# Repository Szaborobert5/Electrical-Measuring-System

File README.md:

# Electrical Measuring System

The PCB was designed in KiCad and firmware was written in STM32CubeIDE. The goal of this project is to develop a device that can measure AC/DC voltage, AC frequency, active power and active energy consumption. This PCB has two layers(signal and ground). 

## Block diagram

The system is divided in 4 sub-systems.

It consists of the following :

- Power supply section
- Microcontroller STM32
- Measuring chip ATM90E26
- OLED Diplay

SPI communication is used for ATM90E26 and OLED display. SWD is used for microcontroller programming. A buck converter is used for power supply

## PCB and Schematic in KiCad

# Firmware

Firmware runs on an **STM32G431K8T6**, reads AC frequency, active power and active energy consumption from an **ATM90E26** metering IC over SPI, and shows the results on an colour display. A push button switches between four screens.

## Firmware architecture

| Module | Files | Responsibility |
|---|---|---|
| Application | `main.c` | Initialisation, 500 ms measurement loop, button handling |
| Metering driver | `atm90e26.c/.h` | ATM90E26 register access, configuration, scaling to physical units |
| Display driver | `st7789.c/.h` | ST7789 initialisation, pixels, lines, rectangles, circles, arcs, text |
| UI | `screens.c/.h` | The four screens, sparkline history, min / max tracking |
| Fonts | `font.c/.h` | Bitmap fonts: 7×10, 11×18, 16×26 |
| Platform | `stm32g4xx_hal_msp.c`, `stm32g4xx_it.c`, `system_stm32g4xx.c`, `syscalls.c`, `sysmem.c` | CubeMX-generated HAL, interrupt and newlib support |

All measurements are stored in one global structure, `g_energy` (`EnergyData_t`), which the metering driver writes and the UI reads.

## Repository structure

```
Core/
  Inc/                        main.h, atm90e26.h, st7789.h, screens.h, font.h, tests.h, ...
  Src/
    main.c                    Application and main loop
    atm90e26.c                Metering IC driver
    st7789.c                  Display driver
    screens.c                 UI screens
    font.c                    Bitmap fonts
    tests.c                   Self-test suite
    stm32g4xx_it.c            Interrupt handlers
    stm32g4xx_hal_msp.c       HAL MSP (SPI1 pins and clocks)
    system_stm32g4xx.c        CMSIS system init
    syscalls.c, sysmem.c      newlib support
Drivers/                      STM32G4 HAL and CMSIS (generated)
Display_Screens.ioc           STM32CubeMX configuration
STM32G431K8TX_FLASH.ld        Linker script
Display_Screens.launch        Run configuration
Display_Screens_Debug.launch  Debug configuration
```

## Testing

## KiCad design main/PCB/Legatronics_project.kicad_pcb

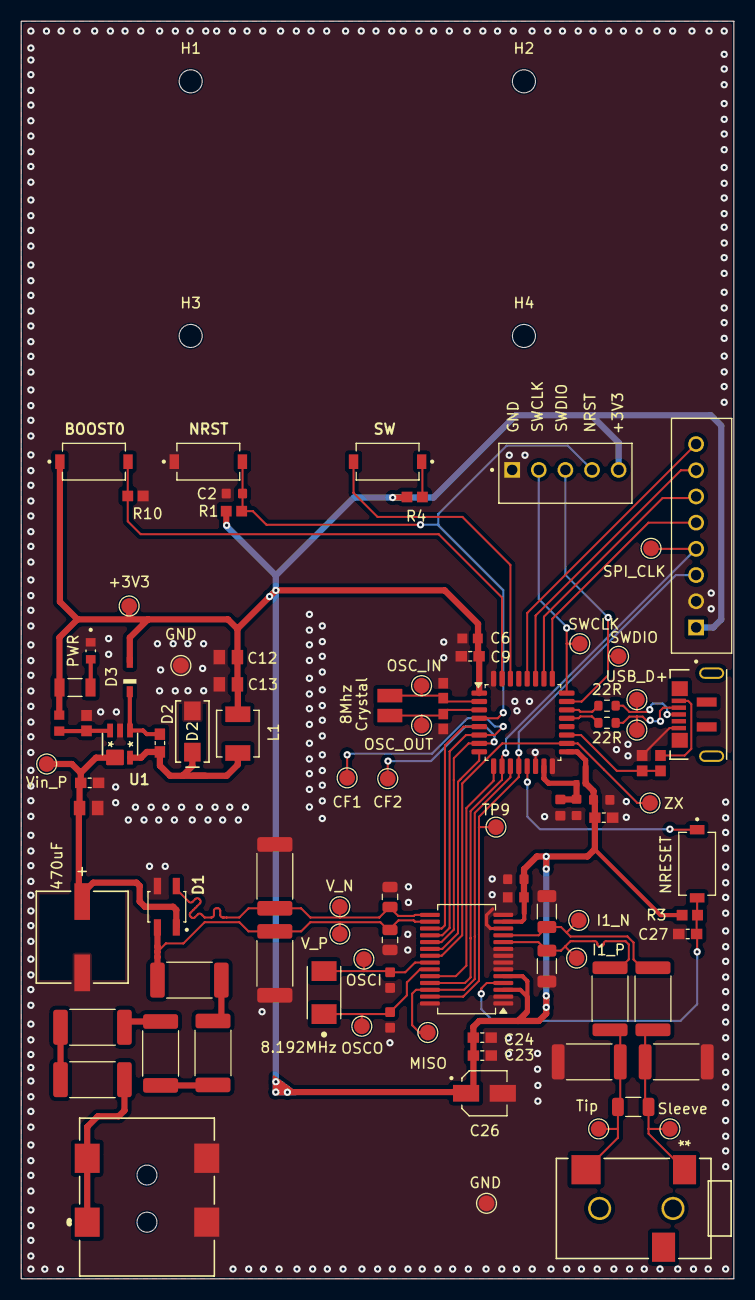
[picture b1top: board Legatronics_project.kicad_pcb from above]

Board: 2 copper layers, 68.0 x 120.0 mm, 98 parts (0 on the bottom side), 50 nets.

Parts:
+3V3: 3V3; TestPoint_Pad_D1.5mm
C1, C3: 8p; CAPC1608X90N
C2, C11, C14, C17: 1uF; CAPC1608X90N
C4: 470uF; PCAP_8x10-ELECT_NCA
C5, C8, C9, C23, C24, C27: 100nF; CAPC1608X90
C6: 4.7uF; CAPC1608X90N
C7, C12, C13: 10uF; CAPC2012X135N
C10: 10nF; CAPC1608X90N
C16, C21: 330nF; C_1206_3216Metric
C18: 1nF; CAPC1608X90N
C19, C20: 33nF; C_0805_2012Metric
C22, C25: 12p; CAPC1608X87N
C26: 10uF; CAP_EEE1CA100SR
CF1: CF1; TestPoint_Pad_D1.5mm
CF2: CF2; TestPoint_Pad_D1.5mm
Cboost1: 100nF; CAPC1608X90
D1: CBRHDSH2-40 TR13 PBFREE; SOIC180P460X187-4N
D2: B240; SMA_DIO-L
D3: 1N4148WS; SODFL2512X100N
D4: PWR; LEDC1608X35N
ECS-81.92-12-30Q-EN-TR1: 8.192MHz; XTAL_ECS-81.92-12-30Q-EN-TR
FB1: 120; BEADC1005X55N
GND: GND; TestPoint_Pad_D1.5mm
GND#2: GND; TestPoint_Pad_D1.5mm
H1, H2, H3, H4: MountingHole; MountingHole_2.2mm_M2
J1: USB-B-1051640001; CON00906_5_MOL
J2: Conn_01x05_Pin; TE_640456-5
J3: PJ-002AH-SMT-TR; PJ-002AH-SMT-TR_CUD
J4: SJ-3523-SMT-TR; SJ-3523-SMT_CUD
J5: B8B-XH-A; JST_B8B-XH-A
L1: 15uH; IND_SRP4020TA-150M
MISO: MISO; TestPoint_Pad_D1.5mm
NDK–STDCRA3-8M1: 8Mhz; XTAL_NX3225GD-8MHZ-STD-CRA-3_NDK
NRESET: PTS636_SM43J_SMTR_LFS; SW_PTS636_SM43J_SMTR_LFS
OSCI: OSCI; TestPoint_Pad_D1.5mm
OSCO: OSCO; TestPoint_Pad_D1.5mm
OSC_IN: OSC_IN; TestPoint_Pad_D1.5mm
OSC_OUT: OSC_OUT; TestPoint_Pad_D1.5mm
R1, R3, R4, R6, R10: 10k; RESC1607X60N
R5: 31.6k; RESC1508X55N
R7, R8: 22R; R_0603_1608Metric
R9: 62R; RESC3116X65N
R12, R13: 100R; R_2512_6332Metric
R14, R18, R19, R20, R21: 3.6k; R_2512_6332Metric_Pad1.40x3.35mm_HandSolder
R15, R16: 2R4; R_2512_6332Metric
R17: 51R; R_1206_3216Metric
R22: 33k; RESC1607X60N
R23: 82k; RESC1607X60N
R24, R25: 1k; R_2512_6332Metric_Pad1.40x3.35mm_HandSolder
S1, S2, S4: PTS636_SM43J_SMTR_LFS; SW_PTS636_SM43J_SMTR_LFS
SPI_CLK: SPI_SCK; TestPoint_Pad_D1.5mm
SWCLK: SWCLK; TestPoint_Pad_D1.5mm
SWDIO: SWDIO; TestPoint_Pad_D1.5mm
Sleeve: Sleeve; TestPoint_Pad_D1.5mm
TP3: I1_P; TestPoint_Pad_D1.5mm
TP4: I1_N; TestPoint_Pad_D1.5mm
TP9: MOSI; TestPoint_Pad_D1.5mm
TP22: Vin_P; TestPoint_Pad_D1.5mm
Tip: Tip; TestPoint_Pad_D1.5mm
U1: MCP16301x-xCH; SOT-23-6_MC_MCH
U2: STM32G431K6Tx; LQFP-32_7x7mm_P0.8mm
U3: ATM90E26-YU; SSOP-28_5.3x10.2mm_P0.65mm
USB_D+: USB_D+; TestPoint_Pad_D1.5mm
USB_D-: USB_D-; TestPoint_Pad_D1.5mm
V_N: IN2_N; TestPoint_Pad_D1.5mm
V_P: V_P; TestPoint_Pad_D1.5mm
ZX: ZX; TestPoint_Pad_D1.5mm

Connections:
+3V3: +3V3.1 (1_1), C6.1, C8.1, C9.1, C12.1, C13.1, C14.1, C17.1, C18.1, C23.1, C24.1, C26.1, D3.A, FB1.2, J2.5, J5.1, L1.2, R1.1, R3.2, R4.1, R5.1, R9.1, S2.1, U2.1 (VDD), U2.17 (VDD), U3.3 (DVDD), U3.5 (AVDD), U3.13 (Vref)
/BOOT0: R10.2, S2.2, U2.31 (PB8)
/Boost: Cboost1.1, D3.C, U1.1 (BOOST)
/CF1: CF1.1 (1_1), U2.6 (PA1), U3.18 (CF1)
/CF2: CF2.1 (1_1), U2.7 (PA2), U3.19 (CF2)
/CS2: U2.9 (PA4), U3.24 (~CS)
/I1_N: C16.2, R13.2, TP4.1 (1_1), U3.11 (I1N)
/I1_P: C21.1, R12.2, TP3.1 (1_1), U3.10 (I1P)
/IRQ: U2.8 (PA3), U3.20 (IRQ)
/LED_A: D4.2, R9.2
/NRESET: NRESET.1, U2.13 (PB0)
/NRST: C2.1, J2.4, R1.2, S1.2, U2.4 (PG10)
/OSCI: C25.1, ECS-81.92-12-30Q-EN-TR1.2, OSCI.1 (1_1), U3.22 (OSCI)
/OSCO: C22.1, ECS-81.92-12-30Q-EN-TR1.1, OSCO.1 (1_1), U3.23 (OSCO)
/OSC_IN: C3.1, NDK–STDCRA3-8M1.2, OSC_IN.1 (1_1), U2.2 (PF0)
/OSC_OUT: C1.1, NDK–STDCRA3-8M1.1, OSC_OUT.1 (1_1), U2.3 (PF1)
/PA9_USB: R22.2, R23.1, U2.19 (PA9)
/PA15_CS1: J5.5, U2.25 (PA15)
/PB3_DISPLAY: J5.6, U2.26 (PB3)
/PB4_RST: J5.7, U2.27 (PB4)
/PB5_BL: J5.8, U2.28 (PB5)
/PB7_SW2: S4.2, U2.30 (PB7)
/SPI_MISO: MISO.1 (1_1), U2.11 (PA6), U3.26 (SDO/UTX)
/SPI_MOSI: J5.3, TP9.1 (1_1), U2.12 (PA7), U3.27 (SDI/URX)
/SPI_SCK: J5.4, SPI_CLK.1 (1_1), U2.10 (PA5), U3.25 (SCLK)
/SW: Cboost1.2, D2.1 (K), L1.1, U1.6 (SW)
/SWCLK: J2.2, SWCLK.1 (1_1), U2.24 (PA14)
/SWDIO: J2.3, SWDIO.1 (1_1), U2.23 (PA13)
/Sleeve: J4.1 (SLEEVE), R13.1, R16.1, R17.1, Sleeve.1 (1_1)
/Tip: J4.2 (TIP), R12.1, R15.2, R17.2, Tip.1 (1_1)
/USB_D+: J1.3, R8.2, USB_D+.1 (1_1)
/USB_D-: J1.2, R7.2, USB_D-.1 (1_1)
/VBUS: J1.1, R22.1
/VDDA: C10.1, C11.1, FB1.1, U2.15 (VDDA)
/VIn_P: C4.1, C5.1, C7.1, D1.1 (+), TP22.1 (1_1), U1.4 (EN), U1.5 (V_{IN})
/V_N: C20.1, D1.2, R25.2, U3.15 (VN), V_N.1 (1_1)
/V_P: C19.1, D1.4, R21.2, R24.2, U3.16 (VP), V_P.1 (1_1)
/Vfb: R5.2, R6.1, U1.3 (Vfb)
/WO: U2.5 (PA0), U3.17 (WarnOut)
/ZX: U2.18 (PA8), U3.21 (ZX), ZX.1 (1_1)
/uC_D+: R8.1, U2.22 (PA12)
/uC_D-: R7.1, U2.21 (PA11)
GND: C1.2, C2.2, C3.2, C4.2, C5.2, C6.2, C7.2, C8.2, C9.2, C10.2, C11.2, C12.2, C13.2, C14.2, C16.1, C17.2, C18.2, C19.2, C20.2, C21.2, C22.2, C23.2, C24.2, C25.2, C26.2, C27.2, D1.3 (-), D2.2 (A), D4.1, GND.1 (1_1), GND#2.1 (1_1), J1.5, J2.1, J3.2, J3.3, J5.2, R6.2, R10.1, R15.1, R16.2, R23.2, R24.1, R25.1, S1.1, U1.2 (GND), U2.14 (VSSA), U2.16 (VSS), U2.32 (VSS), U3.1 (MMD1), U3.2 (DGND), U3.6 (AGND), U3.7 (I2P), U3.8 (I2N), U3.9 (DGND), U3.12 (USEL), U3.14 (AGND), U3.28 (MMD0)
unnamed: J3.1A, J3.1B, R14.1
unnamed: R4.2, S4.1
unnamed: R14.2, R18.1
unnamed: R18.2, R19.1
unnamed: R19.2, R20.1
unnamed: R20.2, R21.1
unnamed: C27.1, NRESET.2, R3.1, U3.4 (~Reset)

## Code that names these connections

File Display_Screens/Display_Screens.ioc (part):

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Mcu.Name=STM32G431K(6-8-B)Tx
Mcu.Package=LQFP32
Mcu.UserName=STM32G431K8Tx
PA0.GPIOParameters=GPIO_Label
PA0.GPIO_Label=WarnOut
PA0.Signal=GPIO_Input
PA1.GPIOParameters=GPIO_Label
PA1.GPIO_Label=CF1
PA1.Signal=GPIO_Input
PA13.Mode=Serial_Wire
PA13.Signal=SYS_JTMS-SWDIO
PA14.Mode=Serial_Wire
PA14.Signal=SYS_JTCK-SWCLK
PA15.GPIOParameters=GPIO_Speed,PinState,GPIO_Label
PA15.GPIO_Label=CS_ST7789
PA15.GPIO_Speed=GPIO_SPEED_FREQ_HIGH
PA15.PinState=GPIO_PIN_SET
PA15.Signal=GPIO_Output
PA2.GPIOParameters=GPIO_Label
PA2.GPIO_Label=CF2
PA2.Signal=GPIO_Input
PA3.GPIOParameters=GPIO_Label
PA3.GPIO_Label=IRQ
PA3.Signal=GPIO_Input
PA4.GPIOParameters=GPIO_Speed,PinState,GPIO_Label
PA4.GPIO_Label=CS_ATM90E26
PA4.GPIO_Speed=GPIO_SPEED_FREQ_HIGH
PA4.PinState=GPIO_PIN_SET
PA4.Signal=GPIO_Output
PA5.Mode=Full_Duplex_Master
PA5.Signal=SPI1_SCK
PA6.Mode=Full_Duplex_Master
PA6.Signal=SPI1_MISO
PA7.Mode=Full_Duplex_Master
PA7.Signal=SPI1_MOSI
PA8.GPIOParameters=GPIO_Label
PA8.GPIO_Label=ZX
PA8.Signal=GPIO_Input
PB0.GPIOParameters=PinState,GPIO_Label
PB0.GPIO_Label=Reset_ATM
PB0.PinState=GPIO_PIN_SET
PB0.Signal=GPIO_Output
PB3.GPIOParameters=GPIO_Speed,GPIO_Label
PB3.GPIO_Label=DC_ST7789
PB3.GPIO_Speed=GPIO_SPEED_FREQ_HIGH
PB3.Signal=GPIO_Output
PB4.GPIOParameters=GPIO_Speed,GPIO_Label
PB4.GPIO_Label=Reset_ST7789
PB4.GPIO_Speed=GPIO_SPEED_FREQ_HIGH
PB4.Signal=GPIO_Output
PB5.GPIOParameters=GPIO_Speed,GPIO_Label
PB5.GPIO_Label=BL_ST7789
PB5.GPIO_Speed=GPIO_SPEED_FREQ_HIGH
PB5.Signal=GPIO_Output
PB7.GPIOParameters=GPIO_PuPd,GPIO_Label
PB7.GPIO_Label=SW2
PB7.GPIO_PuPd=GPIO_PULLUP
PB7.Signal=GPIO_Input
PF0-OSC_IN.Mode=HSE-External-Oscillator
PF0-OSC_IN.Signal=RCC_OSC_IN
PF1-OSC_OUT.Mode=HSE-External-Oscillator
PF1-OSC_OUT.Signal=RCC_OSC_OUT
RCC.HSE_VALUE=8000000
RCC.SYSCLKFreq_VALUE=170000000
RCC.SYSCLKSource=RCC_SYSCLKSOURCE_PLLCLK
board=custom
